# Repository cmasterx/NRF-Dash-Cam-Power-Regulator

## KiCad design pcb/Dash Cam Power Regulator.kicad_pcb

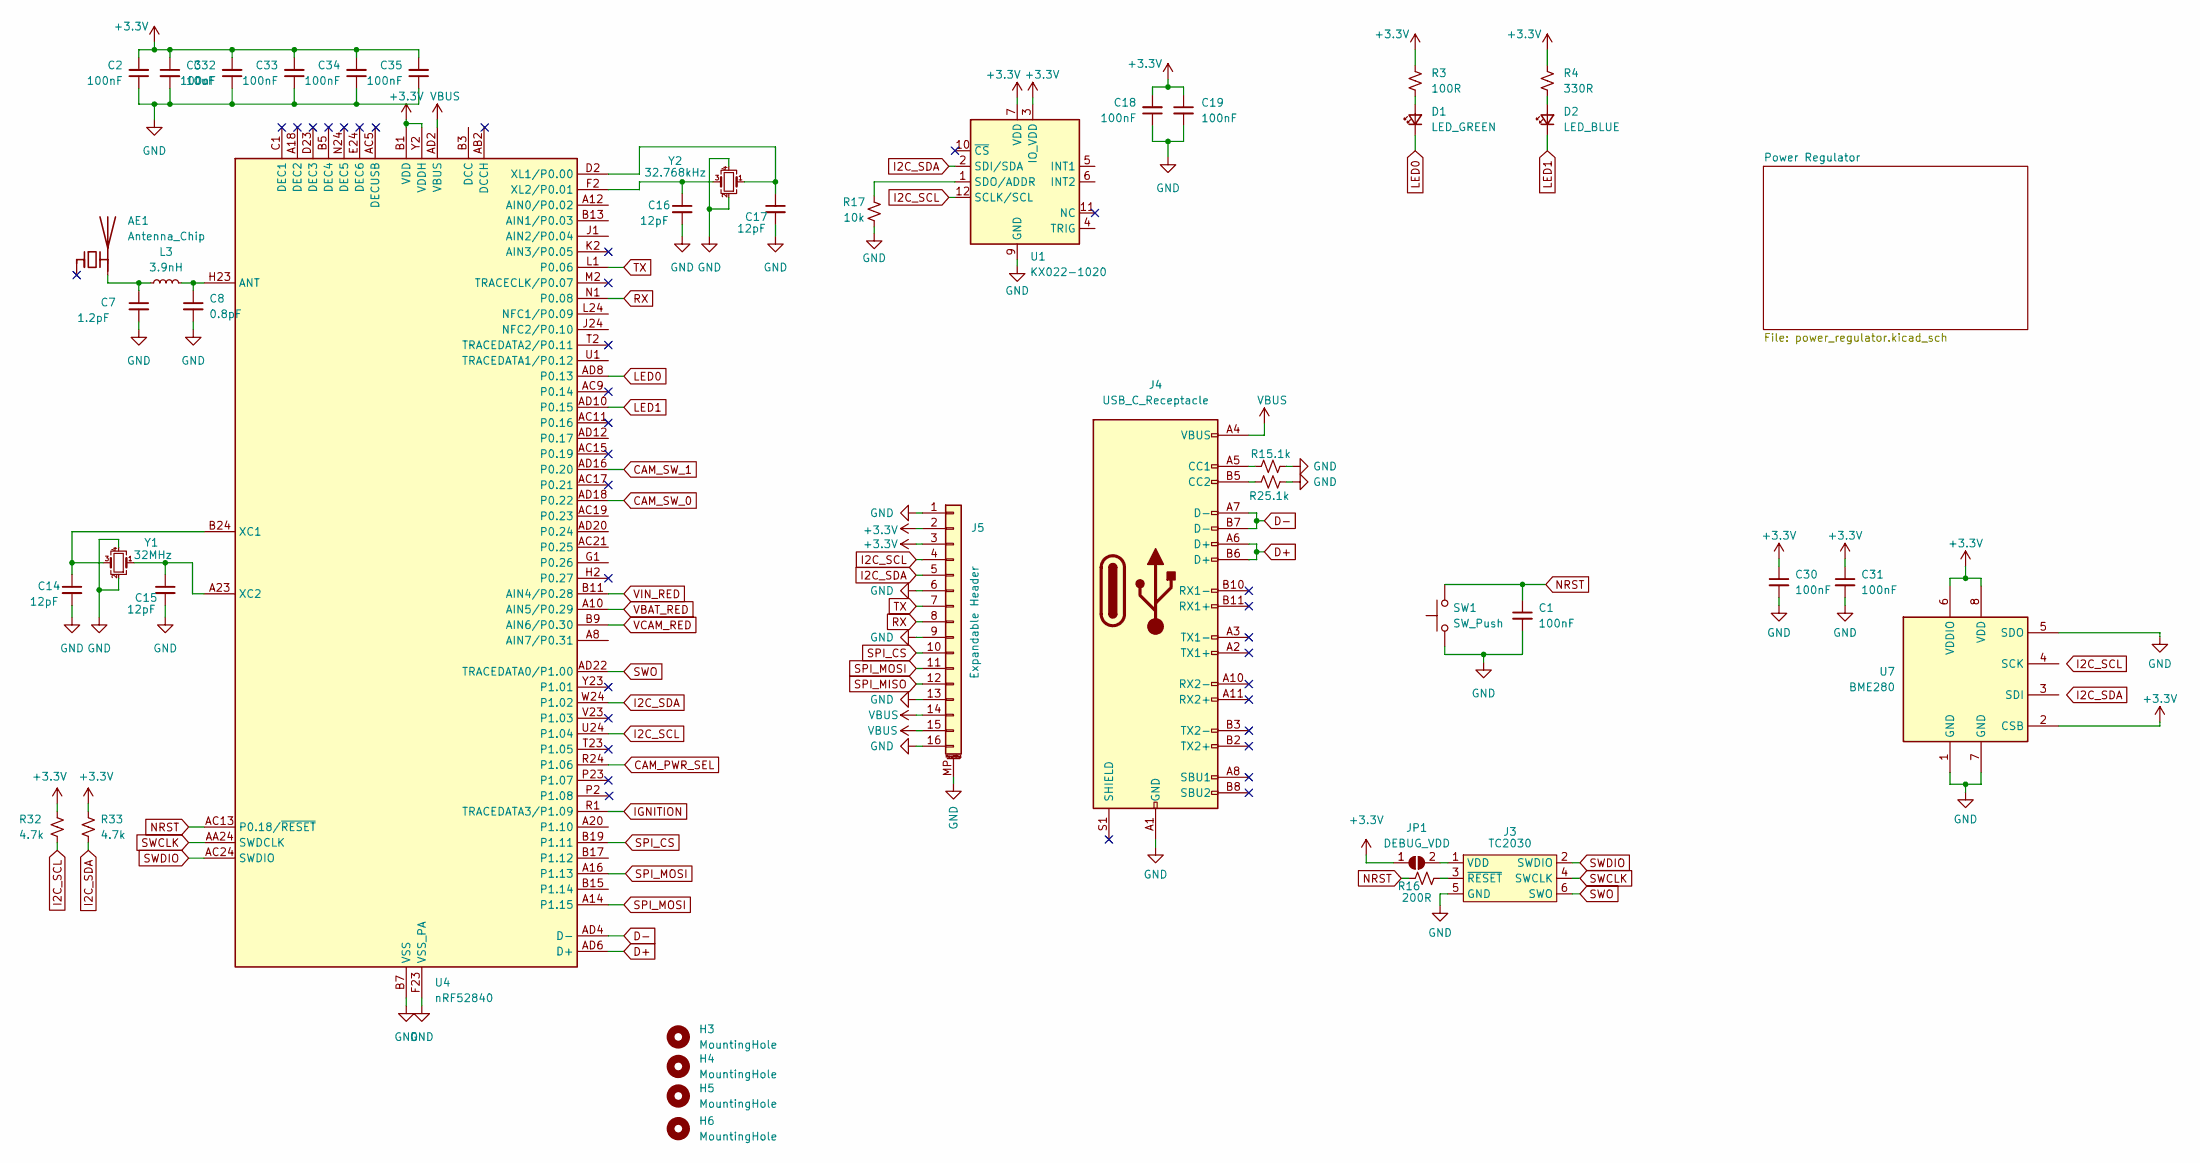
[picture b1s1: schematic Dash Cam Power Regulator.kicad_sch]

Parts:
AE1: Antenna_Chip
C1, C2, C18, C19, C30, C31, C32, C33, C34, C35: 100nF; C_0402_1005Metric
C3: 10uF; C_0603_1608Metric
C7: 1.2pF; C_0402_1005Metric
C8: 0.8pF; C_0402_1005Metric
C14, C15, C16, C17: 12pF; C_0402_1005Metric
D1: LED_GREEN; LED_0805_2012Metric
D2: LED_BLUE; LED_0805_2012Metric
H3, H4, H5, H6: MountingHole; MountingHole_3.2mm_M3_ISO7380_Pad
J3: TC2030; Tag-Connect_TC2030-IDC-NL_2x03_P1.27mm_Vertical
J4: USB_C_Receptacle; USB_C_Receptacle_Amphenol_12401548E4-2A
J5: Expandable Header; JUSHUO-FPC_16
JP1: DEBUG_VDD; SolderJumper-2_P1.3mm_Open_Pad1.0x1.5mm
L3: 3.9nH; L_0402_1005Metric
R1, R2: 5.1k; R_0402_1005Metric
R3: 100R; R_0603_1608Metric
R4: 330R; R_0603_1608Metric
R16: 200R; R_0402_1005Metric
R17: 10k; R_0402_1005Metric
R32, R33: 4.7k; R_0402_1005Metric
SW1: SW_Push; SW_SPST_B3U-1000P
U1: KX022-1020; LGA-12_2x2mm_P0.5mm
U4: nRF52840; Nordic_AQFN-73-1EP_7x7mm_P0.5mm
U7: BME280; Bosch_LGA-8_2.5x2.5mm_P0.65mm_ClockwisePinNumbering
Y1: 32MHz; Crystal_SMD_2016-4Pin_2.0x1.6mm
Y2: 32.768kHz; Crystal_SMD_2016-4Pin_2.0x1.6mm

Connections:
+3V3: C2.2, C3.1, C18.2, C19.1, C30.1, C31.1, C32.2, C33.2, C34.2, C35.2, J5.2, J5.3, JP1.1 (A), R3.1, R4.1, R32.1, R33.1, U1.3 (IO_VDD), U1.7 (VDD), U4.A22 (VDD), U4.AD14 (VDD), U4.AD23 (VDD), U4.B1 (VDD), U4.W1 (VDD), U4.Y2 (VDDH), U7.2 (CSB), U7.6 (VDDIO), U7.8 (VDD); also elsewhere on the board
CAM_PWR_SEL: U4.R24 (P1.06); also elsewhere on the board
CAM_SW_0: U4.AD18 (P0.22); also elsewhere on the board
CAM_SW_1: U4.AD16 (P0.20); also elsewhere on the board
D+: J4.A6 (D+), J4.B6 (D+), U4.AD6 (D+)
D-: J4.A7 (D-), J4.B7 (D-), U4.AD4 (D-)
GND: C1.2, C2.1, C3.2, C7.2, C8.2, C14.2, C15.2, C16.2, C17.2, C18.1, C19.2, C30.2, C31.2, C32.1, C33.1, C34.1, C35.1, J3.5 (GND), J4.A1 (GND), J4.A12 (GND), J4.B1 (GND), J4.B12 (GND), J5.1, J5.6, J5.9, J5.13, J5.16, J5.MP (MountPin), R1.2, R2.2, R17.1, SW1.1, U1.9 (GND), U4.B7 (VSS), U4.EP (VSS), U4.F23 (VSS_PA), U7.1 (GND), U7.5 (SDO), U7.7 (GND), Y1.2, Y1.4, Y2.2, Y2.4; also elsewhere on the board
I2C_SCL: J5.4, R32.2, U1.12 (SCLK/SCL), U4.U24 (P1.04)
I2C_SDA: J5.5, R33.2, U1.2 (SDI/SDA), U4.W24 (P1.02)
IGNITION: U4.R1 (TRACEDATA3/P1.09); also elsewhere on the board
LED0: D1.1 (K), U4.AD8 (P0.13)
LED1: D2.1 (K), U4.AD10 (P0.15)
NRST: C1.1, R16.2, SW1.2, U4.AC13 (P0.18/~RESET)
unnamed: AE1.2 (PCB_Trace), C7.1, L3.1
unnamed: C14.1, U4.B24 (XC1), Y1.3
unnamed: C15.1, U4.A23 (XC2), Y1.1
unnamed: C16.1, U4.F2 (XL2/P0.01), Y2.3
unnamed: C17.1, U4.D2 (XL1/P0.00), Y2.1
unnamed: D1.2 (A), R3.2
unnamed: D2.2 (A), R4.2
unnamed: J3.1 (VDD), JP1.2 (B)
unnamed: J3.3 (~RESET), R16.1
unnamed: J4.A5 (CC1), R1.1
unnamed: J4.B5 (CC2), R2.1
unnamed: R17.2, U1.1 (SDO/ADDR)
unnamed: C8.1, L3.2, U4.H23 (ANT)
RX: J5.8, U4.N1 (P0.08)
SPI_CS: J5.10, U4.B19 (P1.11)
SPI_MISO: J5.12
SPI_MOSI: J5.11, U4.A14 (P1.15), U4.A16 (P1.13)
SWCLK: J3.4 (SWCLK), U4.AA24 (SWDCLK)
SWDIO: J3.2 (SWDIO), U4.AC24 (SWDIO)
SWO: J3.6 (SWO), U4.AD22 (TRACEDATA0/P1.00)
TX: J5.7, U4.L1 (P0.06)
VBAT_RED: U4.A10 (AIN5/P0.29); also elsewhere on the board
VBUS: J4.A4 (VBUS), J4.A9 (VBUS), J4.B4 (VBUS), J4.B9 (VBUS), J5.14, J5.15, U4.AD2 (VBUS)
VCAM_RED: U4.B9 (AIN6/P0.30)
VIN_RED: U4.B11 (AIN4/P0.28); also elsewhere on the board

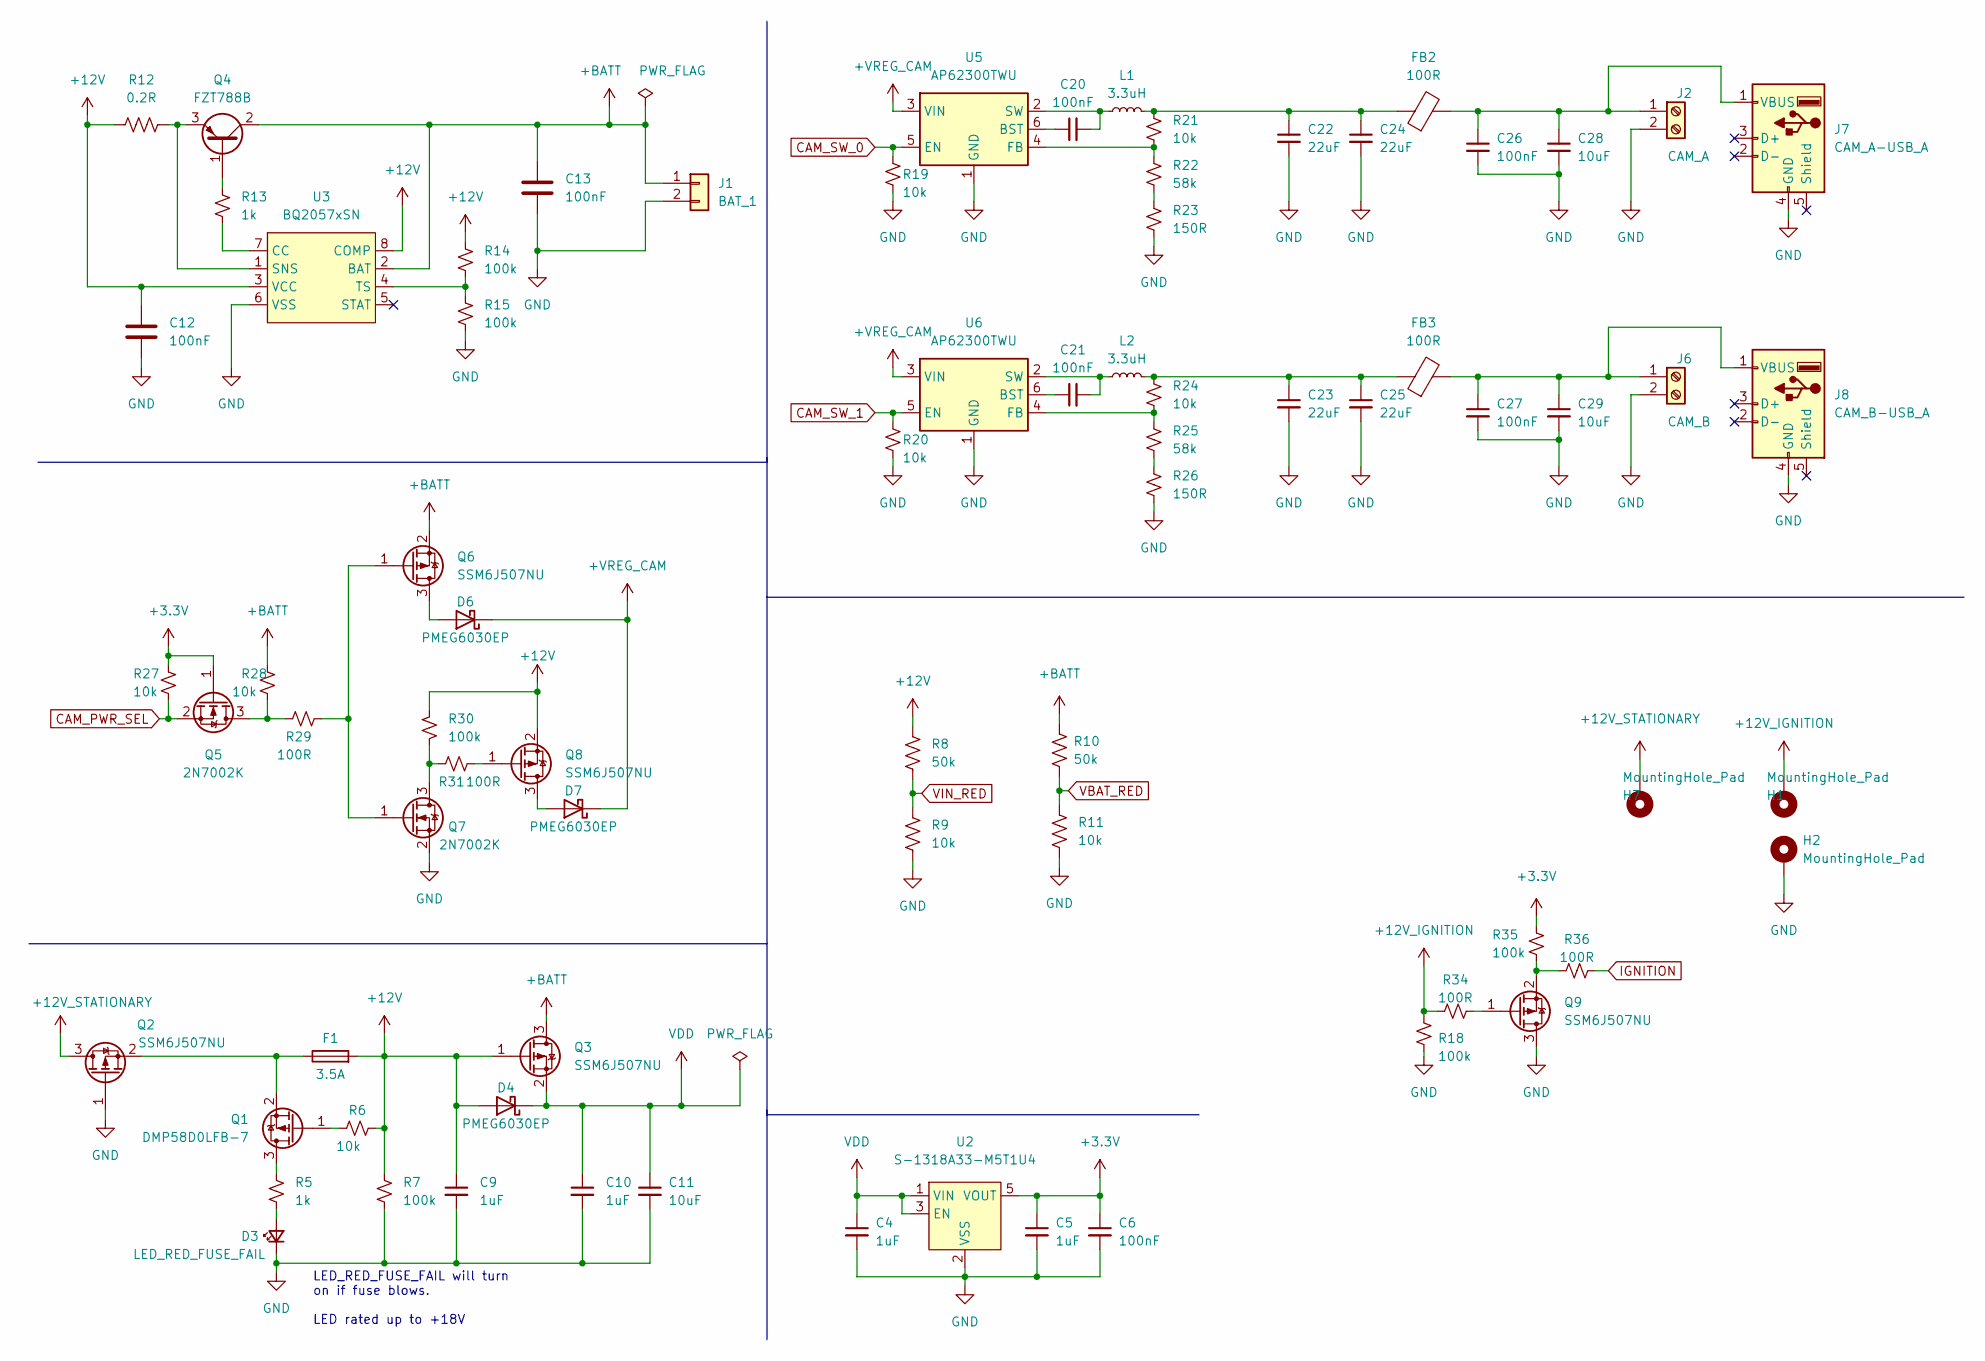
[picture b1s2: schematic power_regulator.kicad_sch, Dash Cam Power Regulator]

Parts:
C4, C5, C9, C10: 1uF; C_0603_1608Metric
C6, C12, C13, C20, C21, C26, C27: 100nF; C_0402_1005Metric
C11: 10uF; C_0805_2012Metric
C22, C23, C24, C25: 22uF; C_0603_1608Metric
C28, C29: 10uF; C_0603_1608Metric
D3: LED_RED_FUSE_FAIL; LED_0603_1608Metric
D4, D6, D7: PMEG6030EP; D_SOD-128
F1: 3.5A; Fuseholder_Littelfuse_Nano2_154x
FB2, FB3: 100R; L_0805_2012Metric
H1, H2, H7: MountingHole_Pad; MountingHole_3.2mm_M3_Pad_Via
J1: BAT_1; AMASS_XT60PW-M
J2: CAM_A; TerminalBlock_Phoenix_MKDS-1,5-2-5.08_1x02_P5.08mm_Horizont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
J6: CAM_B; TerminalBlock_Phoenix_MKDS-1,5-2_1x02_P5.00mm_Horizontal
J7: CAM_A-USB_A; USB_A_Molex_67643_Horizontal
J8: CAM_B-USB_A; USB_A_Molex_67643_Horizontal
L1, L2: 3.3uH; L_0630CDMCCDS-3R3MC
Q1: DMP58D0LFB-7; Diodes_DFN1006-3
Q2, Q3, Q6, Q8, Q9: SSM6J507NU
Q4: FZT788B; SOT-223-3_TabPin2
Q5, Q7: 2N7002K; SOT-23
R5: 1k; R_0603_1608Metric
R6, R9, R11, R19, R20, R21, R24, R27, R28: 10k; R_0402_1005Metric
R7, R14, R15, R18, R30, R35: 100k; R_0402_1005Metric
R8, R10: 50k; R_0402_1005Metric
R12: 0.2R; R_0805_2012Metric
R13: 1k; R_0402_1005Metric
R22, R25: 58k; R_0402_1005Metric
R23, R26: 150R; R_0402_1005Metric
R29, R31, R34, R36: 100R; R_0402_1005Metric
U2: S-1318A33-M5T1U4; SOT-23-5
U3: BQ2057xSN; SOIC-8_3.9x4.9mm_P1.27mm
U5, U6: AP62300TWU; TSOT-23-6

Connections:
+3V3: C5.1, C6.1, Q5.1 (G), R27.1, R35.1, U2.5 (VOUT); also elsewhere on the board
+12V: C9.1, C12.1, D4.2 (A), F1.2, Q3.1 (G), Q8.2 (S), R6.2, R7.1, R8.1, R12.1, R14.1, R30.1, U3.3 (VCC), U3.8 (COMP)
+12V_IGNITION: H1.1, R18.1, R34.1
+12V_STATIONARY: H7.1, Q2.3 (D)
+BATT: C13.1, J1.1, Q3.3 (D), Q4.2 (C), Q6.2 (S), R10.1, R28.1, U3.2 (BAT)
+VREG_CAM: D6.1 (K), D7.1 (K), U5.3 (VIN), U6.3 (VIN)
CAM_PWR_SEL: Q5.2 (S), R27.2; also elsewhere on the board
CAM_SW_0: R19.1, U5.5 (EN); also elsewhere on the board
CAM_SW_1: R20.1, U6.5 (EN); also elsewhere on the board
GND: C4.2, C5.2, C6.2, C9.2, C10.2, C11.2, C12.2, C13.2, C22.2, C23.2, C24.2, C25.2, C26.2, C27.2, C28.2, C29.2, D3.1 (K), H2.1, J1.2, J2.2, J6.2, J7.4 (GND), J8.4 (GND), Q2.1 (G), Q7.2 (S), Q9.3 (D), R7.2, R9.2, R11.2, R15.2, R18.2, R19.2, R20.2, R23.2, R26.2, U2.2 (VSS), U3.6 (VSS), U5.1 (GND), U6.1 (GND); also elsewhere on the board
IGNITION: R36.2; also elsewhere on the board
unnamed: C20.1, U5.6 (BST)
unnamed: C20.2, L1.1, U5.2 (SW)
unnamed: C21.1, U6.6 (BST)
unnamed: C21.2, L2.1, U6.2 (SW)
unnamed: C22.1, C24.1, FB2.1, L1.2, R21.1
unnamed: C23.1, C25.1, FB3.1, L2.2, R24.1
unnamed: C26.1, C28.1, FB2.2, J2.1, J7.1 (VBUS)
unnamed: D3.2 (A), R5.2
unnamed: D6.2 (A), Q6.3 (D)
unnamed: D7.2 (A), Q8.3 (D)
unnamed: F1.1, Q1.2 (S), Q2.2 (S)
unnamed: C27.1, C29.1, FB3.2, J6.1, J8.1 (VBUS)
unnamed: Q1.1 (G), R6.1
unnamed: Q1.3 (D), R5.1
unnamed: Q4.1 (B), R13.1
unnamed: Q4.3 (E), R12.2, U3.1 (SNS)
unnamed: Q5.3 (D), R28.2, R29.1
unnamed: Q6.1 (G), Q7.1 (G), R29.2
unnamed: Q7.3 (D), R30.2, R31.1
unnamed: Q8.1 (G), R31.2
unnamed: Q9.1 (G), R34.2
unnamed: Q9.2 (S), R35.2, R36.1
unnamed: R13.2, U3.7 (CC)
unnamed: R14.2, R15.1, U3.4 (TS)
unnamed: R21.2, R22.1, U5.4 (FB)
unnamed: R22.2, R23.1
unnamed: R24.2, R25.1, U6.4 (FB)
unnamed: R25.2, R26.1
VBAT_RED: R10.2, R11.1; also elsewhere on the board
VDD: C4.1, C10.1, C11.1, D4.1 (K), Q3.2 (S), U2.1 (VIN), U2.3 (EN)
VIN_RED: R8.2, R9.1; also elsewhere on the board

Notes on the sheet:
LED_RED_FUSE_FAIL will turn on if fuse blows. LED rated up to +18V

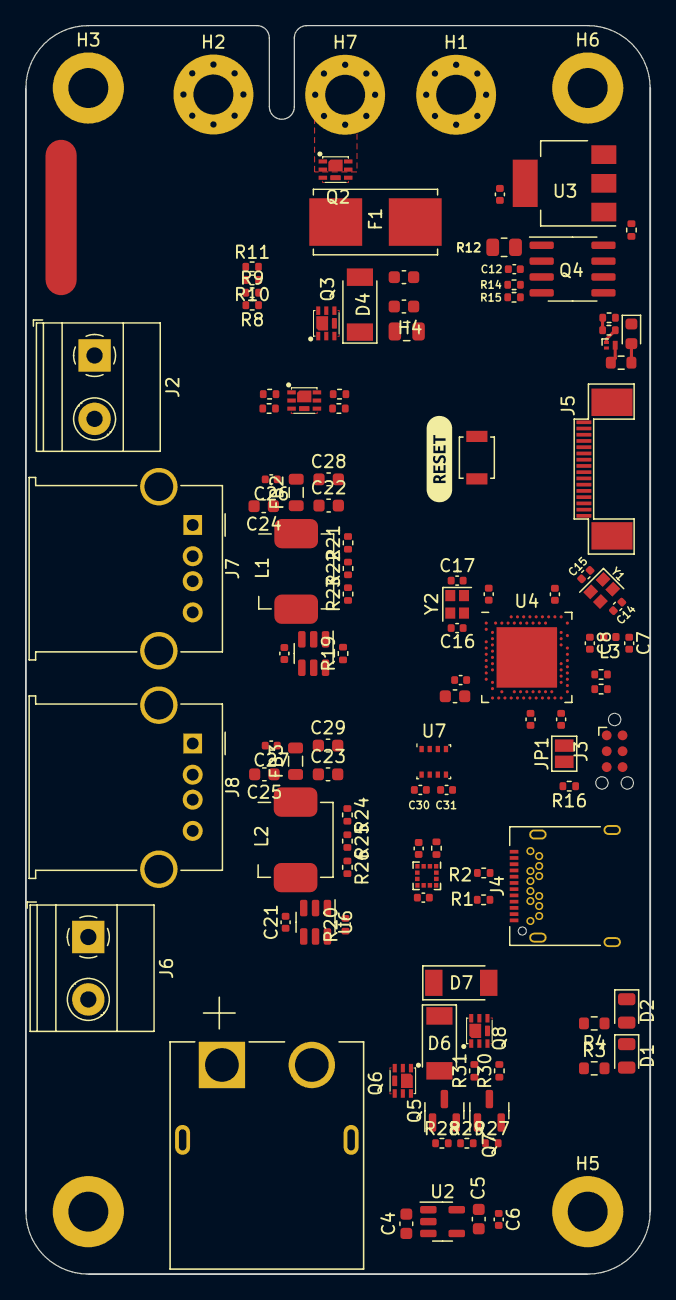
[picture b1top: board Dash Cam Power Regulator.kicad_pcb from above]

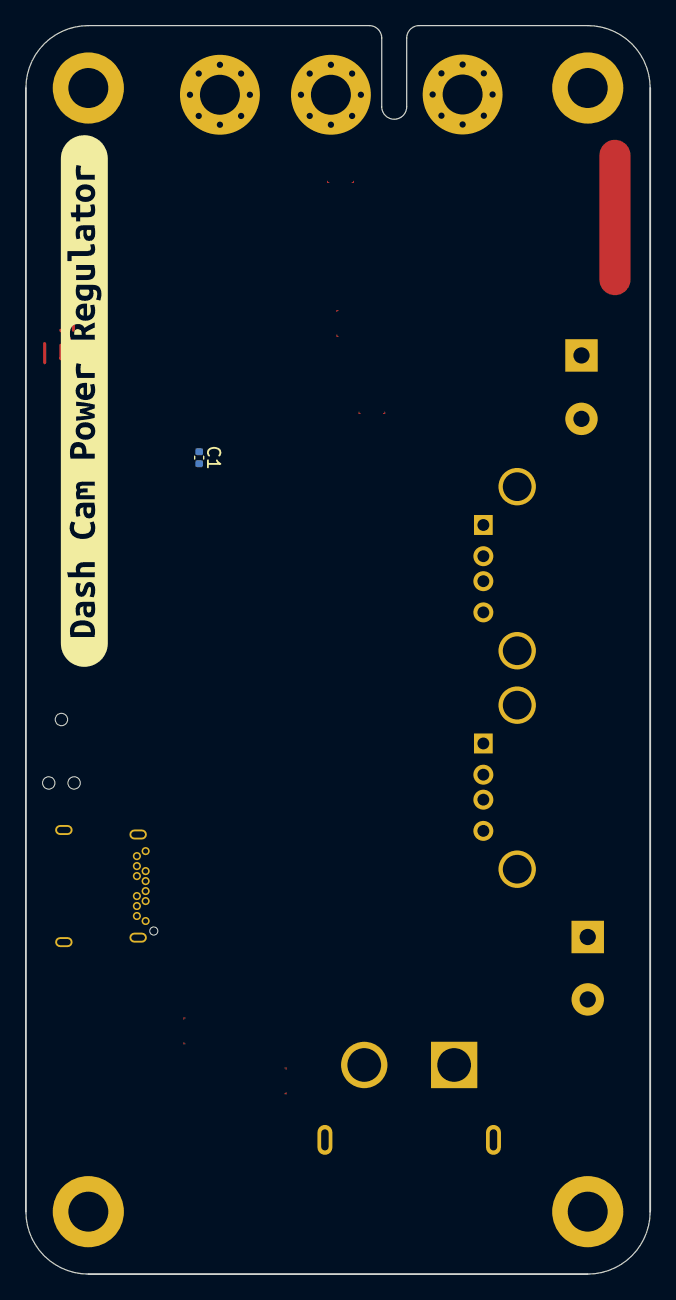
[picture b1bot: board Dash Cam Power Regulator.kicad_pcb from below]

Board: 4 copper layers, 50.0 x 100.0 mm, 120 parts (2 on the bottom side), 70 nets.

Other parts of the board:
kibuzzard-62B547A0: G***; kibuzzard-62B547A0
kibuzzard-62930C1E: G***; kibuzzard-62930C1E

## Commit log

2023-01-03 Initial pcb project push
